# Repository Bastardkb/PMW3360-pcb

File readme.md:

Outdated

Use https://github.com/Bastardkb/charybdis-pmw-sensor

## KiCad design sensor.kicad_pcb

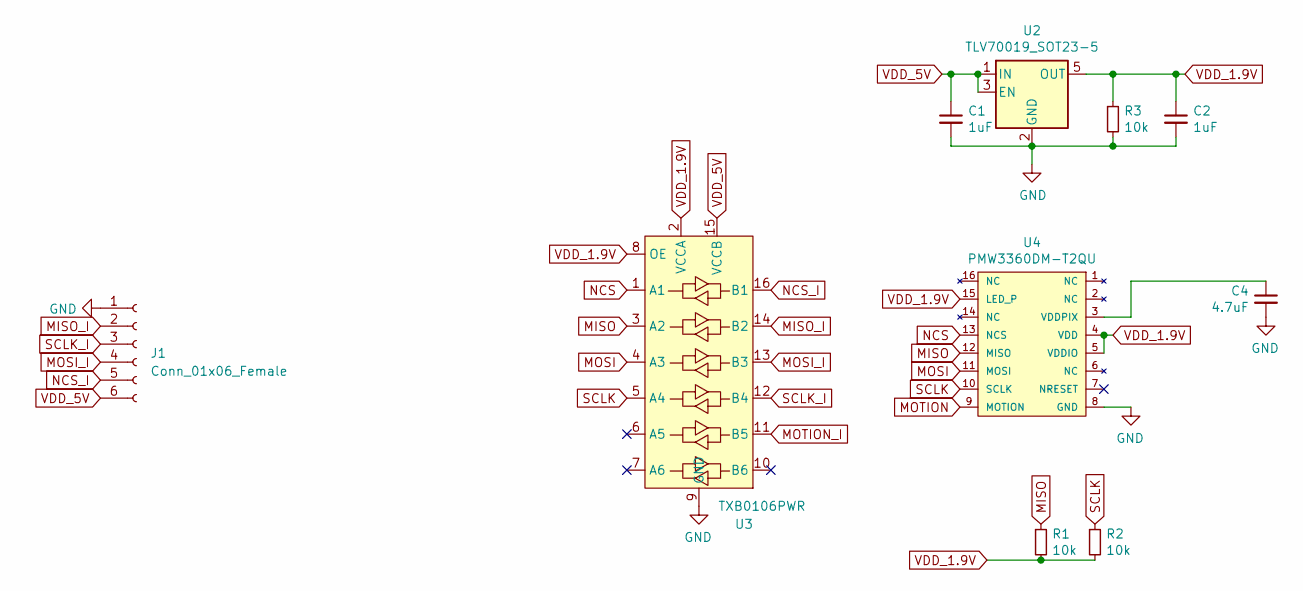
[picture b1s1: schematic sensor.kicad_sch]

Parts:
C1, C2: 1uF; C_0805_2012Metric_Pad1.15x1.40mm_HandSolder; JLCPCB Part #（optional） C28323
C4: 4.7uF; C_0805_2012Metric_Pad1.15x1.40mm_HandSolder; JLCPCB Part #（optional） C1779
J1: Conn_01x06_Female; PinHeader_1x06_P2.54mm_Vertical
R1, R2, R3: 10k; R_0805_2012Metric_Pad1.15x1.40mm_HandSolder; JLCPCB Part #（optional） C17414
U2: TLV70019_SOT23-5; SOT-23-5_HandSoldering
U3: TXB0106PWR; TSSOP-16_4.4x5mm_P0.65mm
U4: PMW3360DM-T2QU; DIP-16_W10.16mm

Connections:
GND: C1.2, C2.2, C4.2, J1.1, R3.2, U2.2 (GND), U3.9 (GND), U4.8 (GND)
MISO: R1.1, U3.3 (A2), U4.12 (MISO)
MISO_I: J1.2, U3.14 (B2)
MOSI: U3.4 (A3), U4.11 (MOSI)
MOSI_I: J1.4, U3.13 (B3)
MOTION: U4.9 (MOTION)
MOTION_I: U3.11 (B5)
NCS: U3.1 (A1), U4.13 (NCS)
NCS_I: J1.5, U3.16 (B1)
unnamed: C4.1, U4.3 (VDDPIX)
SCLK: R2.1, U3.5 (A4), U4.10 (SCLK)
SCLK_I: J1.3, U3.12 (B4)
VDD_1.9V: C2.1, R1.2, R2.2, R3.1, U2.5 (OUT), U3.2 (VCCA), U3.8 (OE), U4.4 (VDD), U4.5 (VDDIO), U4.15 (LED_P)
VDD_5V: C1.1, J1.6, U2.1 (IN), U2.3 (EN), U3.15 (VCCB)

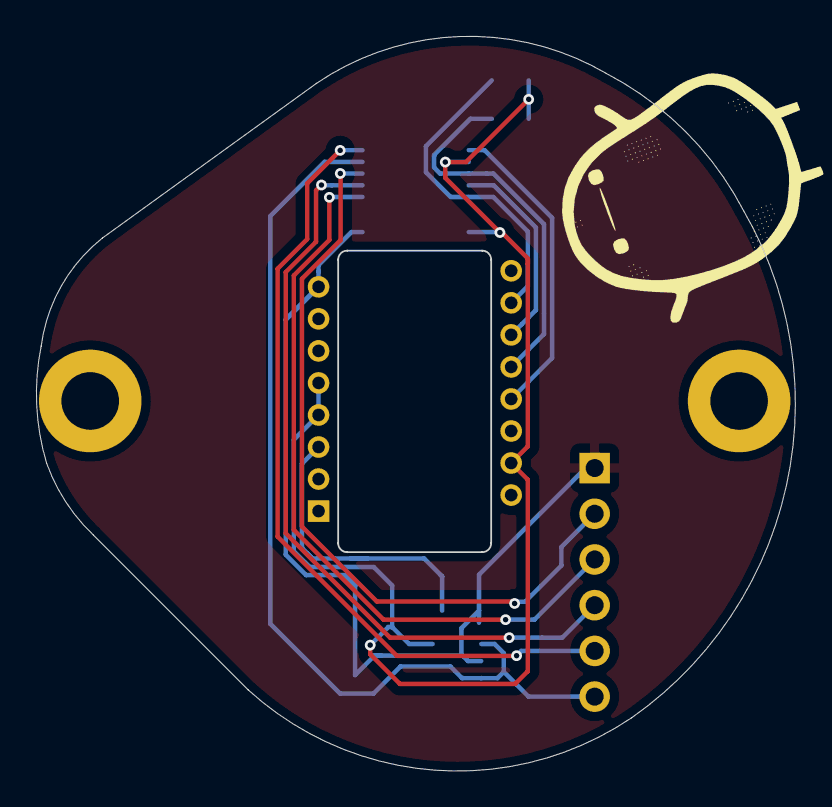
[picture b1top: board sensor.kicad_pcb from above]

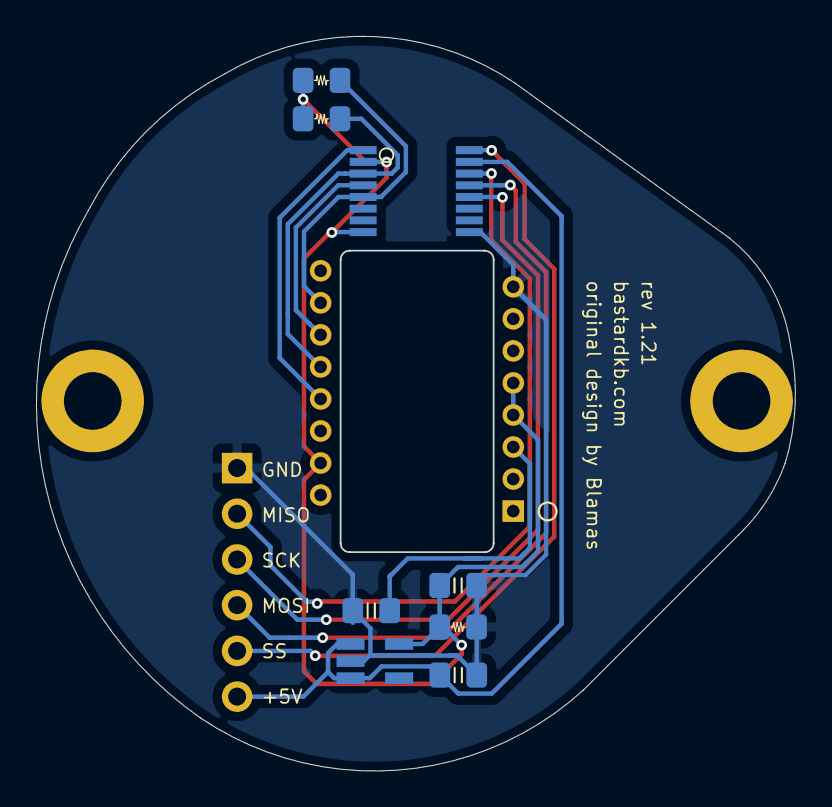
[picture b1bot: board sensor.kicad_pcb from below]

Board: 2 copper layers, 42.2 x 40.8 mm, 10 parts (9 on the bottom side), 12 nets.

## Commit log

2021-06-12 switch to M3 and header pins
2021-06-12 silkscreen
2021-06-12 slightly bigger edge cuts for M3 holes
2021-06-28 remove useless files, add gitignore
2021-06-28 more cleanup
2021-06-28 add description and pics
2021-07-07 routing
2021-07-21 screw clearance, edge cuts
2021-07-22 add detrompeur
2021-07-22 edge cuts and logo
2021-08-10 restart project
